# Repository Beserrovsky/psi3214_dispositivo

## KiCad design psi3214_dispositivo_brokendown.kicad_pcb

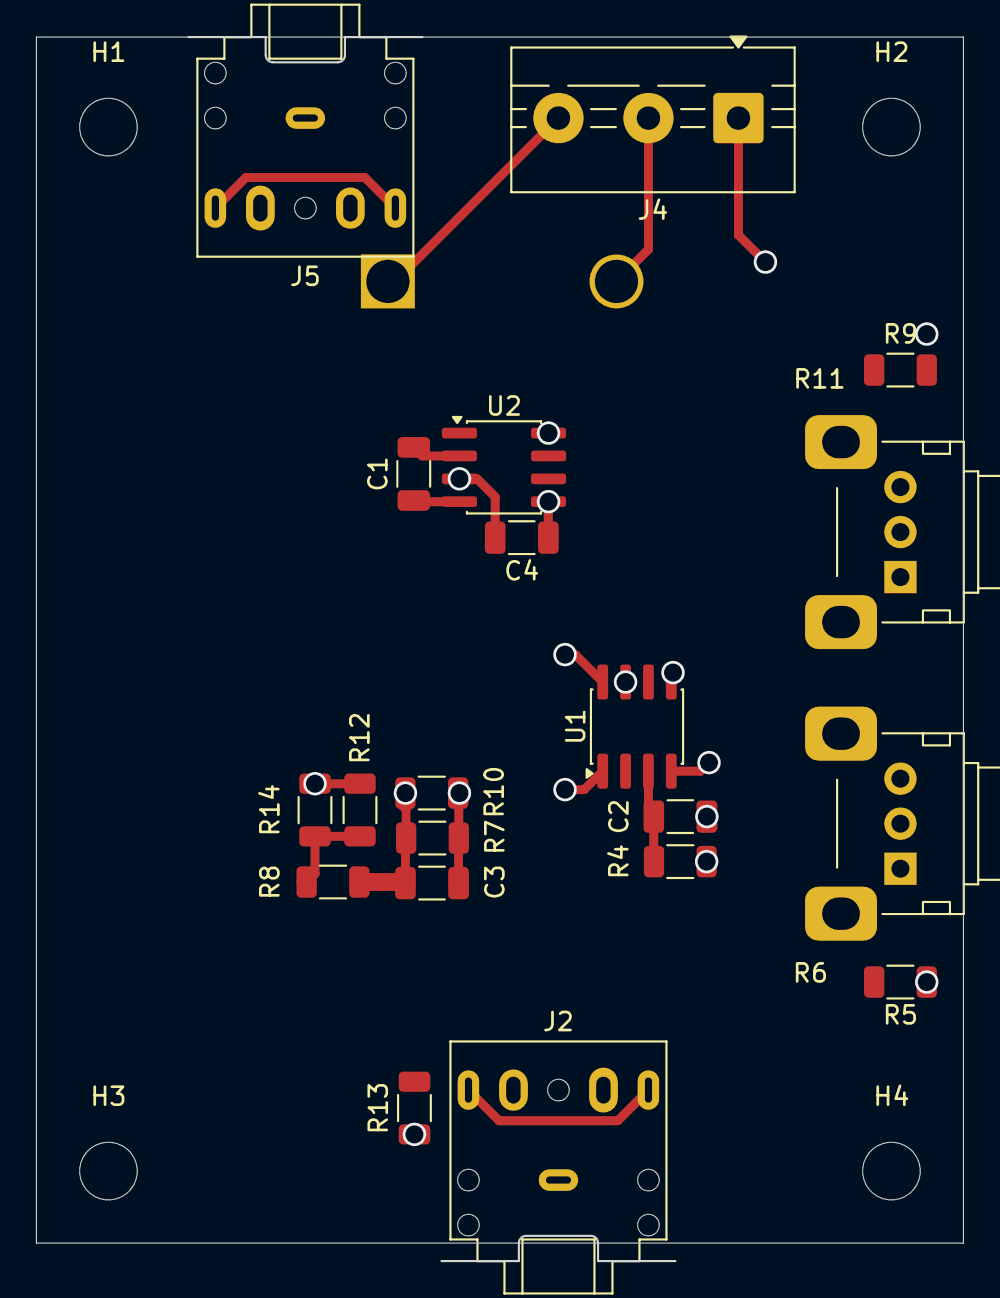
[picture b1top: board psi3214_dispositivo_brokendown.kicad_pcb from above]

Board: 2 copper layers, 51.5 x 68.0 mm, 25 parts (1 on the bottom side), 13 nets.

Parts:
BT1: Battery; BatteryHolder_Eagle_12BH611-GR
C1, C4: 10u; C_1206_3216Metric
C2: 1u; C_1206_3216Metric
C3: 10n; C_1206_3216Metric
H1, H2, H3, H4: MountingHole; MountingHole_3.2mm_M3
J2, J5: AudioJack3; Jack_3.5mm_CUI_SJ1-3525N_Horizontal
J4: Conn_01x03; TerminalBlock_MaiXu_MX126-5.0-03P_1x03_P5.00mm
R4, R13: 10k; R_1206_3216Metric
R5, R8, R9: 1k; R_1206_3216Metric
R6, R11: Potentiometer; Potentiometer_Alps_RK09K_Single_Horizontal
R7: 68k; R_1206_3216Metric
R10: 1M; R_1206_3216Metric
R12: 1.5k; R_1206_3216Metric
R14: 3.3k; R_1206_3216Metric
U1: TL072_sim; SOIC-8_3.9x4.9mm_P1.27mm
U2: MAX1044; SOIC-8_3.9x4.9mm_P1.27mm

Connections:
+9V: BT1.1 (+), J4.3, U1.8 (V+), U2.8 (V+)
-9V: C4.1, J4.1, U1.4 (V-), U2.5 (VOUT)
GND: BT1.2 (-), C4.2, J2.S, J4.2, J5.S, R4.1, R5.1, R9.1, R12.1, R13.2, R14.1, U2.3 (GND)
unnamed: R8.1, R12.2, R14.2
unnamed: R5.2, R6.2, U1.2 (-)
unnamed: R9.2, R11.2, U1.6 (-)
unnamed: C1.1, U2.2 (CAP+)
unnamed: C1.2, U2.4 (CAP-)
entrada: C2.1, J5.R, J5.T
saida: J2.R, J2.T, R11.1, R13.1, U1.7
saida_amp1: C3.1, R6.1, R7.1, R10.1, U1.1
saida_cap: C2.2, R4.2, U1.3 (+)
saida_filtro: C3.2, R7.2, R8.2, R10.2, U1.5 (+)
